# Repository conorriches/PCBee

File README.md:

# PCbee
Mancunian themed wearable badge and nice "my first soldering" project.

## Design
Designed in Kicad with the help of @GregNGM.

## Reference
The Mancehster Bee has been a symbol of Manchester since the industrial revolution.

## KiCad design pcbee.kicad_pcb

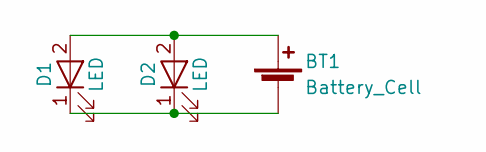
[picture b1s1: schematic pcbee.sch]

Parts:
BT1: Battery_Cell; Keystone_103_1x20mm-CoinCell
D1, D2: LED; LED_D5.0mm

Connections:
unnamed: BT1.1 (+), D1.2 (A), D2.2 (A)
unnamed: BT1.2 (-), D1.1 (K), D2.1 (K)

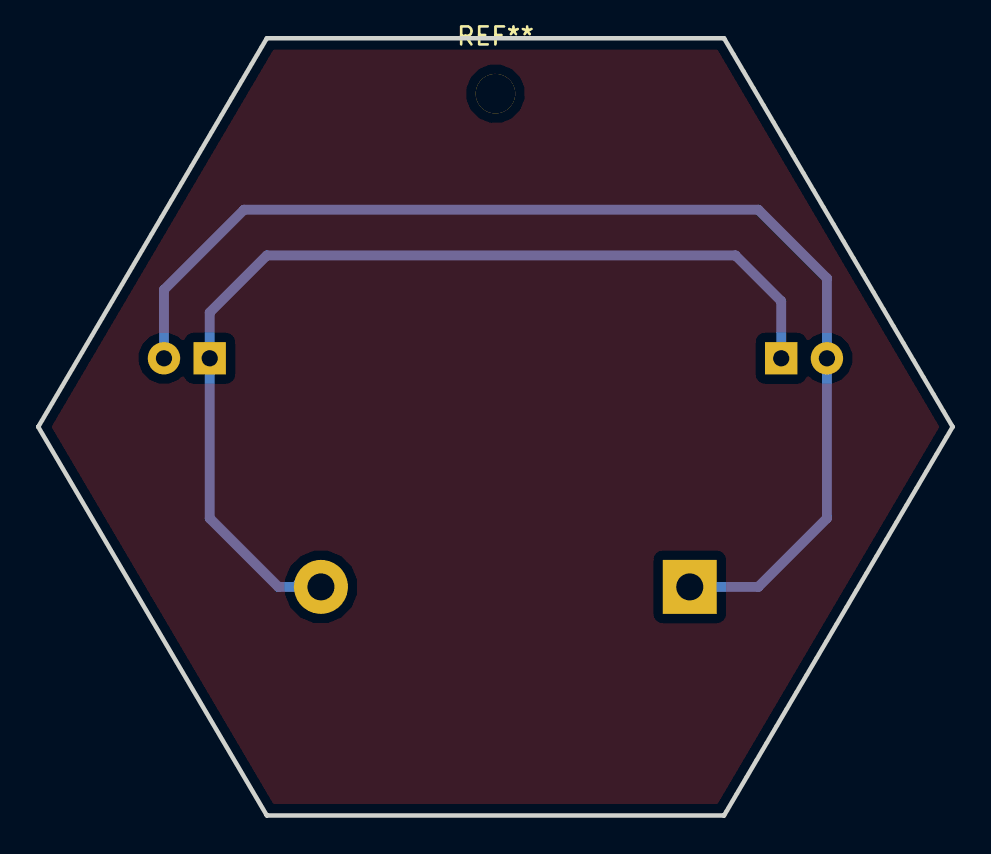
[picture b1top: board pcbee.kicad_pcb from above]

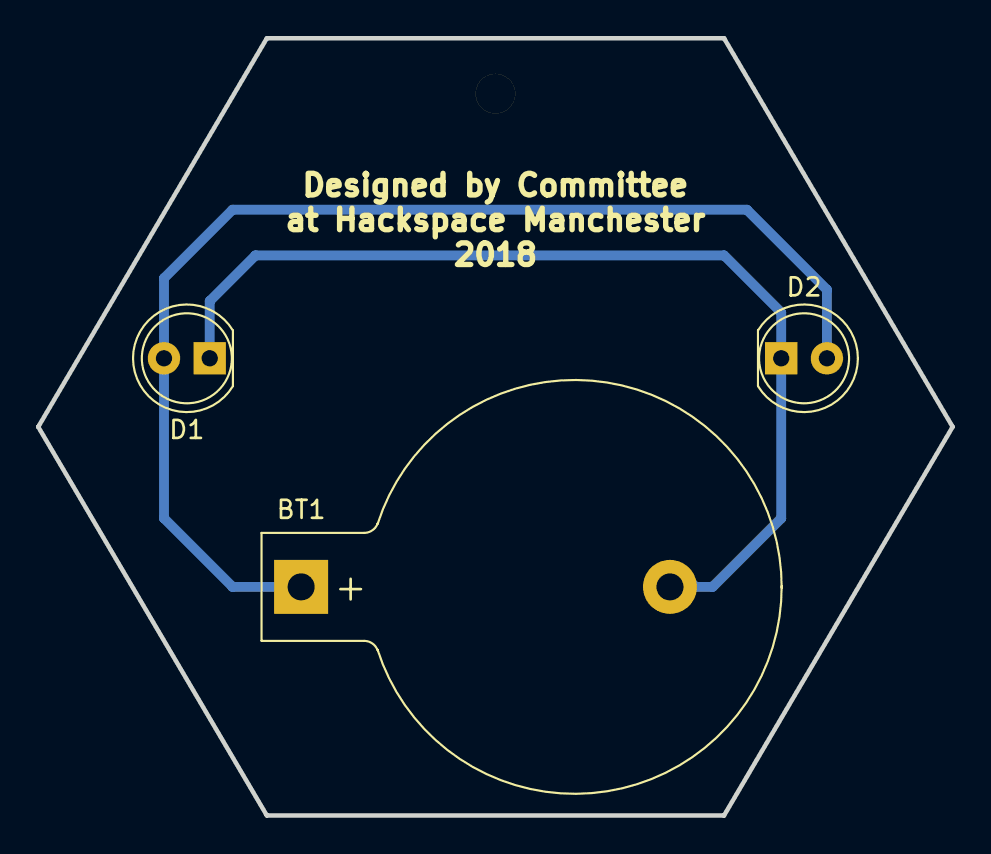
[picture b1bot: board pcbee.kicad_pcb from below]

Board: 2 copper layers, 50.8 x 43.2 mm, 3 parts (3 on the bottom side), 2 nets.

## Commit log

2018-03-10 Fixed top fill, minor placement and routing changes.
    Top fill redone to remove shorts.
    Battery holder moved to prevent encroachment on design
    This has resulted in the outline of the battery holder being over the pin, but as it is on the back and the battery holder has standoffs it should not interfere.
2018-03-10 Created gerbers
    Created gerbers from latest commit.
2018-03-11 I fixed it (#1)
    * Fixed top fill, minor placement and routing changes.
    Top fill redone to remove shorts.
    Battery holder moved to prevent encroachment on design
    This has resulted in the outline of the battery holder being over the pin, but as it is on the back and the battery holder has standoffs it should not interfere.
    * Created gerbers
    Created gerbers from latest commit.
2018-03-14 Changed text to be degigned by committee
2018-03-14 Generate gerbers
2018-04-05 fix the conflicts
2018-04-05 move mounting hole
2018-04-05 readme
2018-04-05 closed kicad and this happened
2018-04-07 Created Gerbers and checked (#3)
